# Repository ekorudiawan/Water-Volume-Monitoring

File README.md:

# Water-Volume-Monitoring
Water Volume Monitoring Using Arduino

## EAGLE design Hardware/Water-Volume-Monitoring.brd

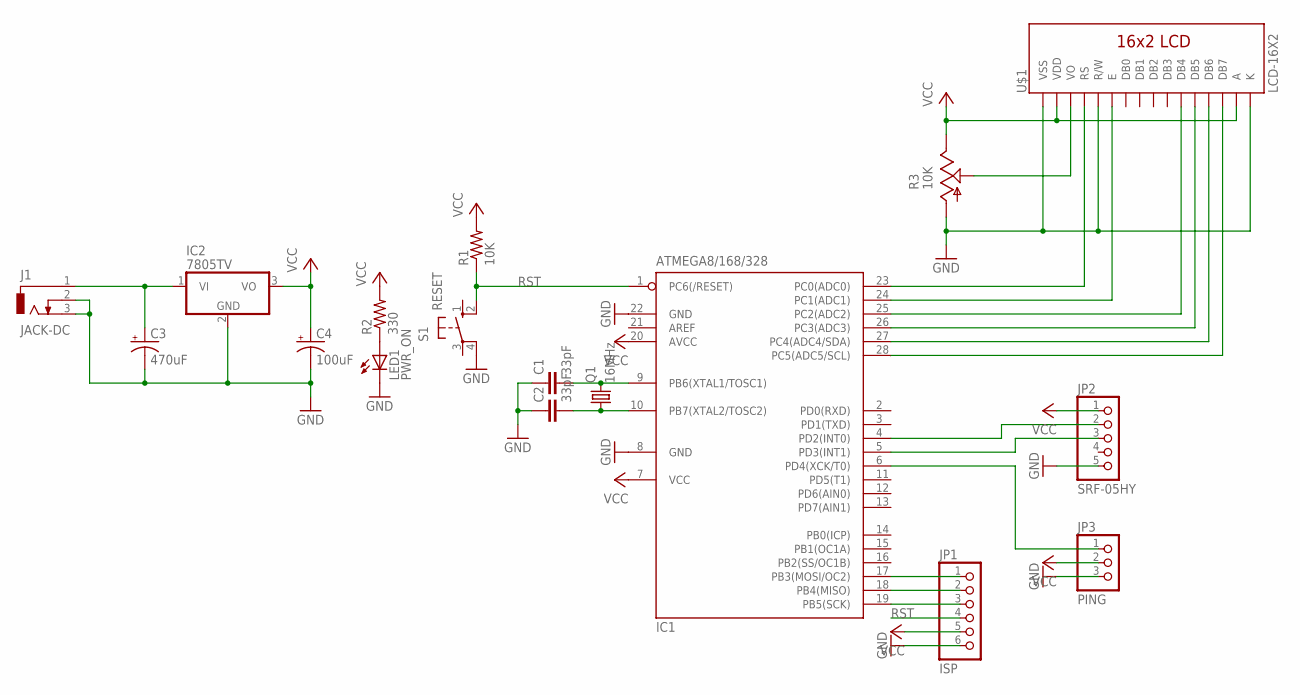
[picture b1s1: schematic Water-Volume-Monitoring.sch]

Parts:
C1, C2: 33pF; C025-024X044
C3: 470uF; E2,5-6
C4: 100uF; E2,5-6
IC1: ATMEGA8/168/328; DIL28-3
IC2: 7805TV; TO220V
J1: JACK-DC; DCJ0202
JP1: ISP; 1X06
JP2: SRF-05HY; 1X05
JP3: PING; 1X03
LED1: PWR_ON; LED3MM
Q1: 16MHz; HC49/S
R1: 10K; 0207/10
R2: 330; 0207/10
R3: 10K; CA6V
S1: RESET; B3F-10XX
U$1: LCD-16X2

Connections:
GND: C1.1, C2.1, C3.-, C4.-, IC1.8 (GND), IC1.22 (GND), IC2.2 (GND), J1.2, J1.3, JP1.6, JP2.5, JP3.3, LED1.K (C), R3.A, S1.4 (P1), U$1.1 (VSS), U$1.5 (R/W), U$1.16 (K)
unnamed: C1.2, IC1.9 (PB6(XTAL1/TOSC1)), Q1.2
unnamed: C2.2, IC1.10 (PB7(XTAL2/TOSC2)), Q1.1
unnamed: IC1.4 (PD2(INT0)), JP2.2
unnamed: C3.+, IC2.1 (VI), J1.1
unnamed: IC1.5 (PD3(INT1)), JP2.3
unnamed: IC1.6 (PD4(XCK/T0)), JP3.1
unnamed: LED1.A, R2.1
unnamed: R3.S, U$1.3 (VO)
unnamed: IC1.23 (PC0(ADC0)), U$1.4 (RS)
unnamed: IC1.24 (PC1(ADC1)), U$1.6 (E)
unnamed: IC1.25 (PC2(ADC2)), U$1.11 (DB4)
unnamed: IC1.26 (PC3(ADC3)), U$1.12 (DB5)
unnamed: IC1.27 (PC4(ADC4/SDA)), U$1.13 (DB6)
unnamed: IC1.28 (PC5(ADC5/SCL)), U$1.14 (DB7)
unnamed: IC1.17 (PB3(MOSI/OC2)), JP1.1
unnamed: IC1.18 (PB4(MISO)), JP1.2
unnamed: IC1.19 (PB5(SCK)), JP1.3
RST: IC1.1 (PC6(/RESET)), JP1.4, R1.1, S1.2 (S1)
VCC: C4.+, IC1.7 (VCC), IC1.20 (AVCC), IC2.3 (VO), JP1.5, JP2.1, JP3.2, R1.2, R2.2, R3.E, U$1.2 (VDD), U$1.15 (A)

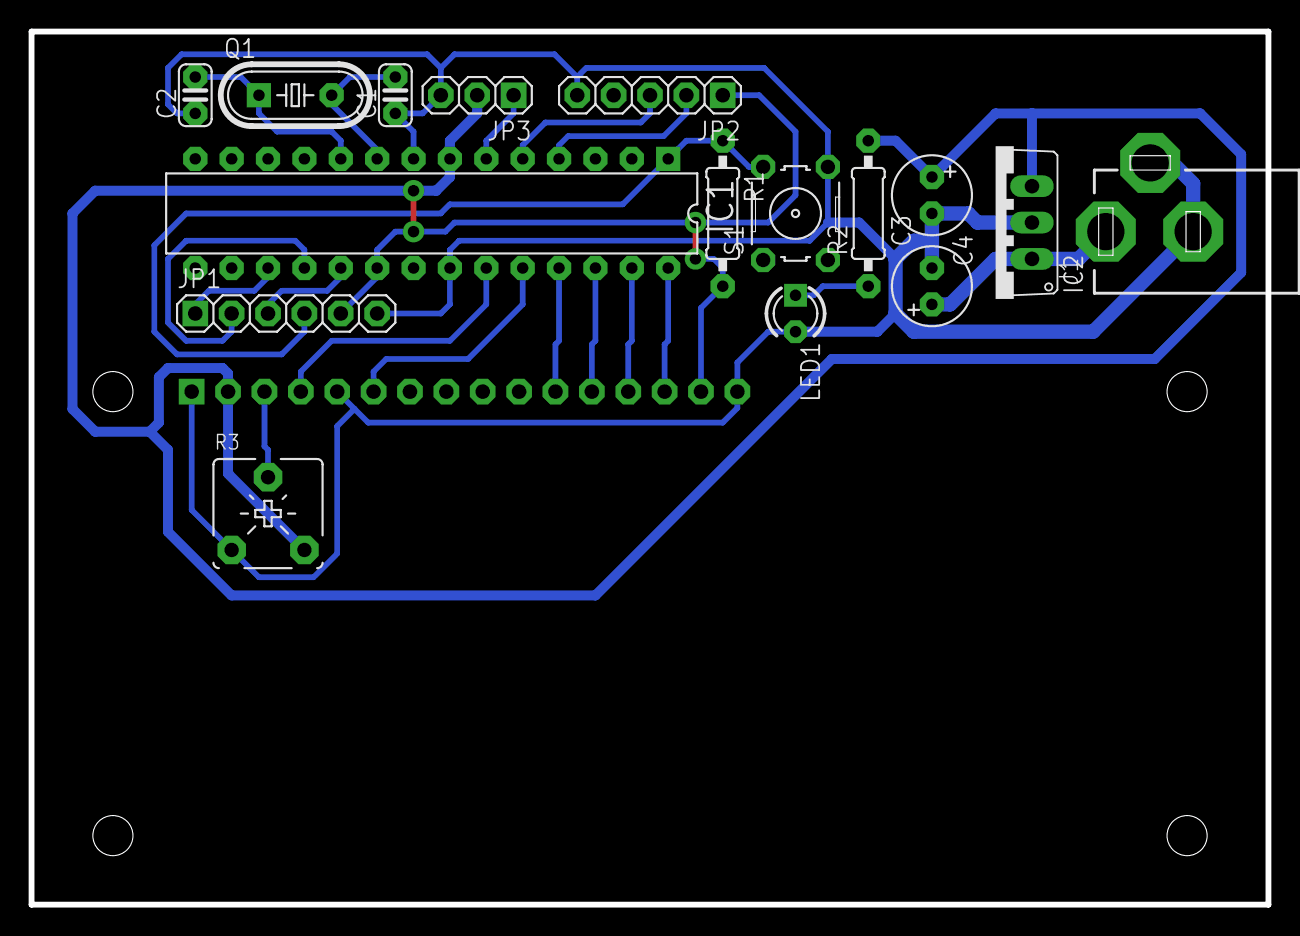
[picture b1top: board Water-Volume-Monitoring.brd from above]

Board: 2 copper layers, 86.4 x 61.0 mm, 17 parts (0 on the bottom side), 20 nets.

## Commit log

2017-10-03 Added HW & SW Files
